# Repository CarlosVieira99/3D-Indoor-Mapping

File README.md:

# 3D-Indoor-Mapping
Final year's bachelor project and report with a final classification of 19 (scale of 0 - 20). Development of a 3D Scanner for indoor spaces with applications related to architecture and civil engineering.

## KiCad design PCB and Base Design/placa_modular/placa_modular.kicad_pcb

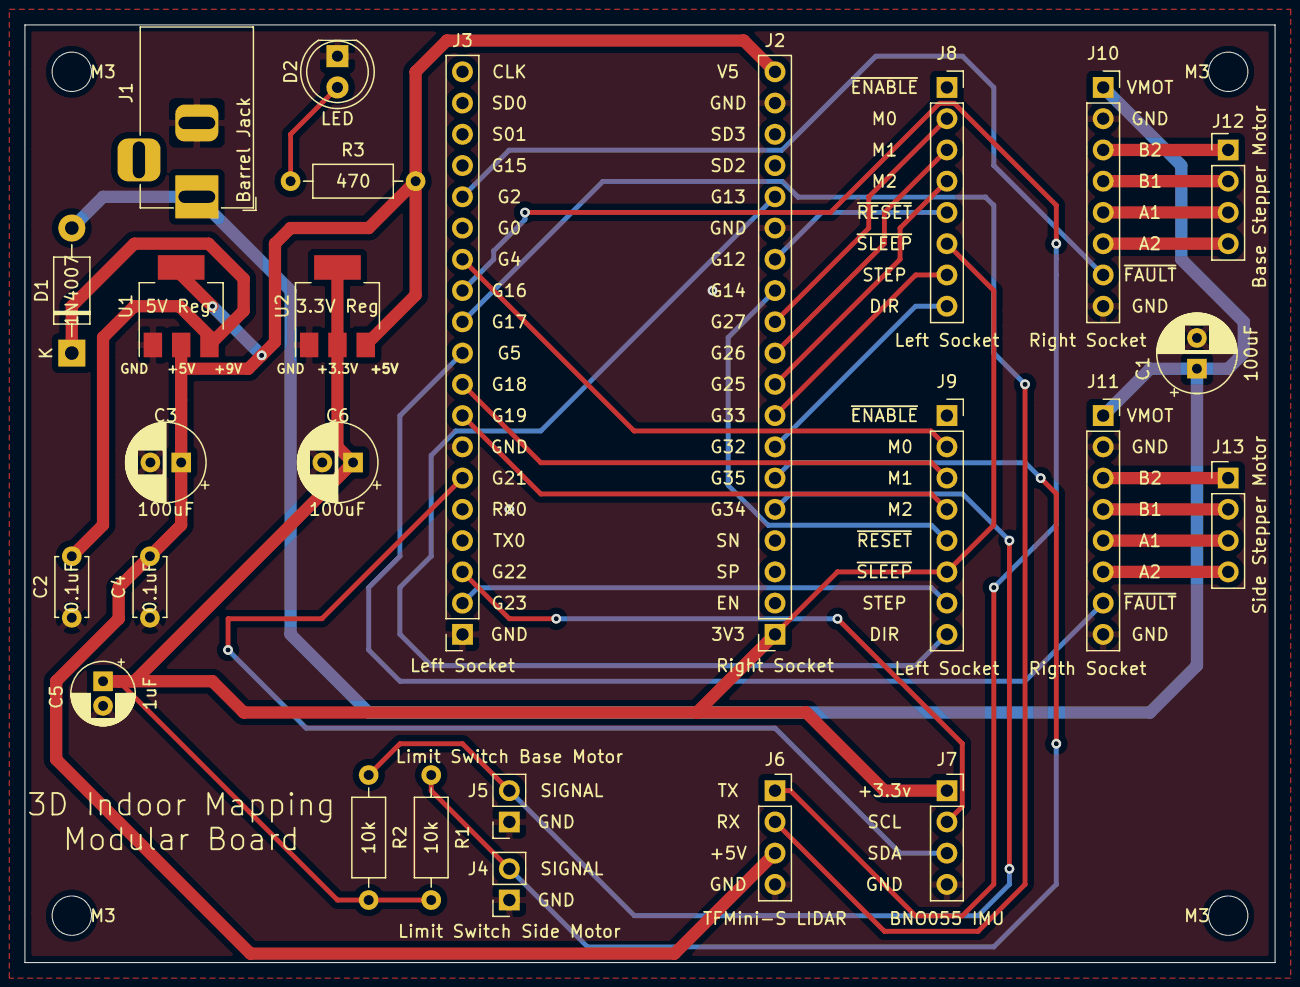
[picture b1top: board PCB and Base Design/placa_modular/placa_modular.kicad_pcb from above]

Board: 2 copper layers, 101.6 x 76.2 mm, 26 parts (0 on the bottom side), 34 nets.

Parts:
C1, C3, C6: 100uF; CP_Radial_D6.3mm_P2.50mm
C2, C4: 0.1uF; C_Disc_D4.7mm_W2.5mm_P5.00mm
C5: 1uF; CP_Radial_D5.0mm_P2.00mm
D1: 1N4007; D_DO-41_SOD81_P10.16mm_Horizontal
D2: LED; LED_D5.0mm
J1: Barrel Jack; BarrelJack_Horizontal
J2: Right Socket; PinSocket_1x19_P2.54mm_Vertical
J3: Left Socket; PinSocket_1x19_P2.54mm_Vertical
J4: Limit Switch Side Motor; PinSocket_1x02_P2.54mm_Vertical
J5: Limit Switch Base Motor; PinSocket_1x02_P2.54mm_Vertical
J6: TFMini-S LIDAR; PinSocket_1x04_P2.54mm_Vertical
J7: BNO055 IMU; PinSocket_1x04_P2.54mm_Vertical
J8, J9: Left Socket; PinSocket_1x08_P2.54mm_Vertical
J10: Right Socket; PinSocket_1x08_P2.54mm_Vertical
J11: Rigth Socket; PinSocket_1x08_P2.54mm_Vertical
J12: Base Stepper Motor; PinHeader_1x04_P2.54mm_Vertical
J13: Side Stepper Motor; PinHeader_1x04_P2.54mm_Vertical
R1, R2: 10k; R_Axial_DIN0207_L6.3mm_D2.5mm_P10.16mm_Horizontal
R3: 470; R_Axial_DIN0207_L6.3mm_D2.5mm_P10.16mm_Horizontal
U1: 5V Reg.; SOT-223-3_TabPin2
U2: 3.3V Reg; SOT-223-3_TabPin2

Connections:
3.3V: C5.1, C6.1, J2.1, J7.1, J8.6, J9.6, R1.1, R2.1, U2.2
5V: C3.1, C4.1, J2.19, J6.3, R3.1, U1.2, U2.3
A1_B: J10.5, J12.3
A1_S: J11.5, J13.3
A2_B: J10.6, J12.4
A2_S: J11.6, J13.4
B1_B: J10.4, J12.2
B1_S: J11.4, J13.2
B2_B: J10.3, J12.1
B2_S: J11.3, J13.1
DIR_B: J2.7, J8.8
DIR_S: J2.15, J9.8
G2: J3.15, J10.7
G4: J3.13, J9.2
G5: J3.10, J11.7
G12: J2.13, J8.5
G14: J2.12, J9.5
G16: J3.12, J6.1
G17: J3.11, J6.2
G18: J3.9, J9.3
G19: J3.8, J9.4
G21: J3.6, J7.3
G22: J3.3, J7.2
G23: J3.2, J9.7
G25: J2.9, J8.4
G26: J2.10, J8.3
G27: J2.11, J8.2
G33: J2.8, J8.7
G34: J2.5, J5.2, R2.2
G35: J2.6, J4.2, R1.2
GND: C1.2, C2.2, C3.2, C4.2, C5.2, C6.2, D2.1, J1.2, J2.14, J2.18, J3.1, J3.7, J4.1, J5.1, J6.4, J7.4, J10.2, J10.8, J11.2, J11.8, U1.1, U2.1
M_VCC_B: C1.1, D1.2, J1.1, J10.1, J11.1
unnamed: C2.1, D1.1, U1.3
unnamed: D2.2, R3.2

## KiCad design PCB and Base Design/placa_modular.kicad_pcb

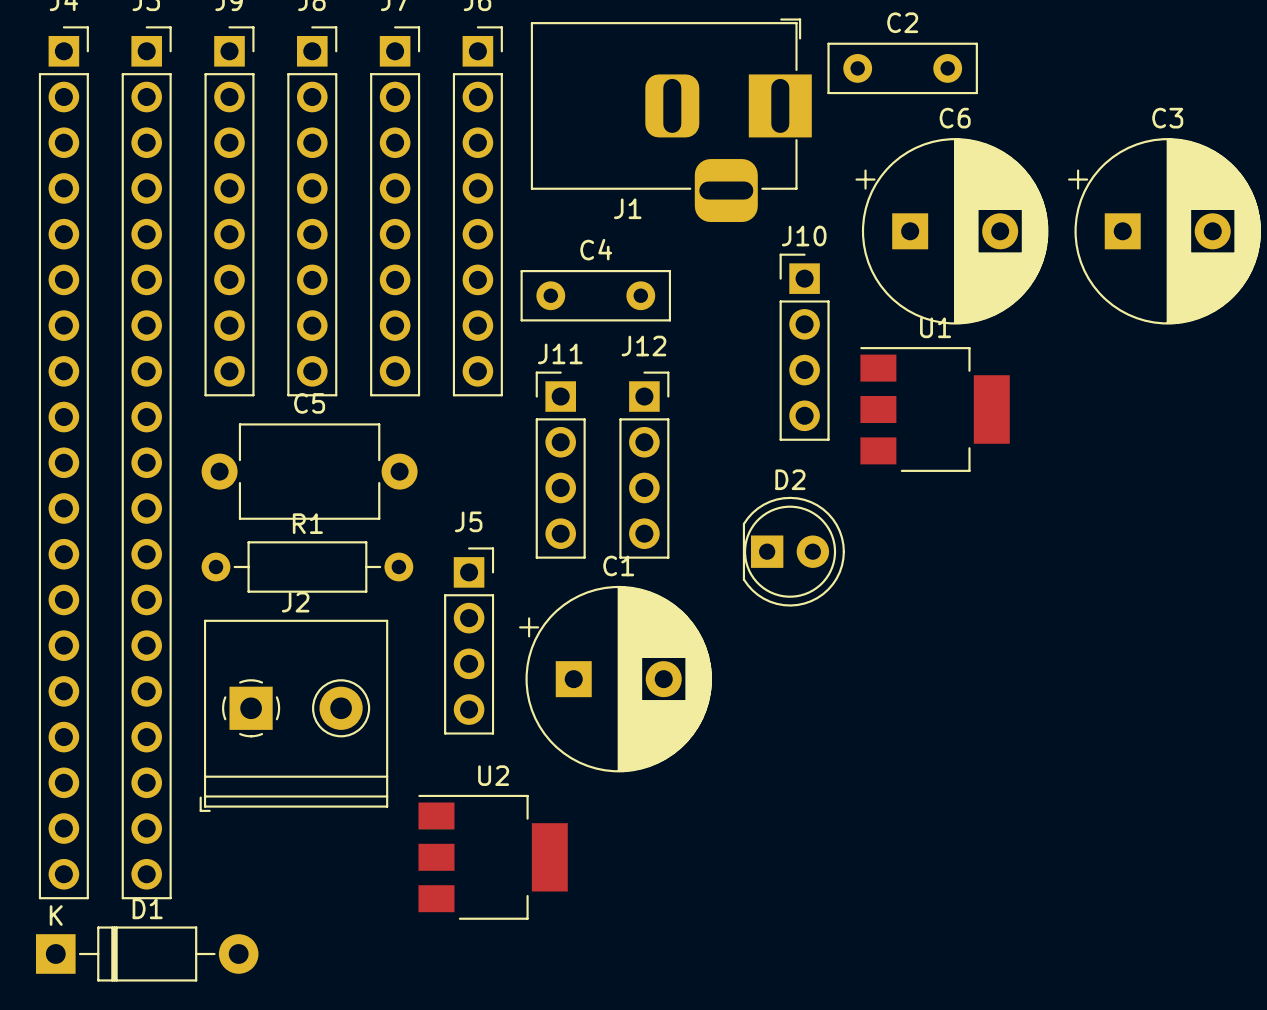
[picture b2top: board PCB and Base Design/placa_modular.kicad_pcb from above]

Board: 2 copper layers, 23 parts (0 on the bottom side), 28 nets, no tracks yet.

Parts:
C1, C3, C6: 100uF; CP_Radial_D10.0mm_P5.00mm
C2, C4: 0.1uF; C_Disc_D8.0mm_W2.5mm_P5.00mm
C5: 1uF; C_Disc_D7.5mm_W5.0mm_P10.00mm
D1: 1N4007; D_DO-41_SOD81_P10.16mm_Horizontal
D2: LED; LED_D5.0mm
J1: Barrel_Jack; BarrelJack_Horizontal
J2: Input_Alternative; TerminalBlock_Philmore_TB132_1x02_P5.00mm_Horizontal
J3: ESP32_E; PinSocket_1x19_P2.54mm_Vertical
J4: ESP32_D; PinSocket_1x19_P2.54mm_Vertical
J5: BNO055; PinSocket_1x04_P2.54mm_Vertical
J6: DRV8825_B_E; PinSocket_1x08_P2.54mm_Vertical
J7: DRV8825_S_E; PinSocket_1x08_P2.54mm_Vertical
J8: DRV8825_B_D; PinSocket_1x08_P2.54mm_Vertical
J9: DRV8825_S_D; PinSocket_1x08_P2.54mm_Vertical
J10: DRV8825_S_MOTOR; PinHeader_1x04_P2.54mm_Vertical
J11: DRV8825_B_MOTOR; PinHeader_1x04_P2.54mm_Vertical
J12: TFMini-S; PinSocket_1x04_P2.54mm_Vertical
R1: 470; R_Axial_DIN0207_L6.3mm_D2.5mm_P10.16mm_Horizontal
U1: AMS1117-5.0; SOT-223-3_TabPin2
U2: AMS1117-3.3; SOT-223-3_TabPin2

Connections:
3.3V: C5.1, C6.1, J3.1, J5.1, J6.5, J6.6, J7.5, J7.6, U2.2
5V: C3.1, C4.1, J3.19, J12.3, R1.1, U1.2, U2.3
A1_B: J8.5, J10.3
A1_S: J9.5, J11.3
A2_B: J8.6, J10.4
A2_S: J9.6, J11.4
B1_B: J8.4, J10.2
B1_S: J9.4, J11.2
B2_B: J8.3, J10.1
B2_S: J9.3, J11.1
DIR_B: J3.7, J6.8
DIR_S: J3.15, J7.8
G4: J4.13, J7.2
G16: J4.12, J12.1
G17: J4.11, J12.2
G18: J4.9, J7.3
G19: J4.8, J7.4
G21: J4.6, J5.3
G22: J4.3, J5.2
G23: J4.2, J7.7
G25: J3.9, J6.4
G26: J3.10, J6.3
G27: J3.11, J6.2
G33: J3.8, J6.7
GND: C1.2, C2.2, C3.2, C4.2, C5.2, C6.2, D2.1, J1.2, J2.2, J3.14, J3.18, J4.1, J4.7, J5.4, J8.2, J8.8, J9.2, J9.8, J12.4, U1.1, U2.1
M_VCC_B: C1.1, D1.2, J1.1, J2.1, J8.1, J9.1
unnamed: C2.1, D1.1, U1.3
unnamed: D2.2, R1.2
